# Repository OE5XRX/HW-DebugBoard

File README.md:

# HW-DebugBoard

Ein universelles Debug-Board für die OE5XRX-Modulplattform zur Entwicklung, Analyse und automatisierten Tests von Hardware-Modulen wie z. B. dem FM-Transceiver-Modul.

## Features

- USB-C + USB-Hub für:
  - Debug-STM32 (Firmwaretest)
  - ST-Link zur Programmierung
  - USB-Verbindung zum DUT
- Schnittstelle für genormte DUT-Module (2×10 Pin)
- INA226 für Strom- und Spannungsmessung
- OLED-Display und Taster zur Steuerung
- Erweiterbar durch GPIO, ADC, DAC, UARTs, I²C

## Projektstatus

🛠️ Derzeit in Schaltungsdesign-Phase (Schematic)

---

## ✅ To-do Liste (Schaltplan – Hierarchisch)

### 🔌 1. USB & USB-Hub (`usb_hub.sch`)
- [x] USB-C Buchse mit ESD-Schutz (TVS)
- [x] USB-Hub IC (z. B. FS1.1, TUSB2046B, GL850G)
- [x] Downstream-Port 1: Debug-STM32
- [x] Downstream-Port 2: ST-Link USB
- [x] Downstream-Port 3: DUT USB-Buchse
- [x] Taktquelle für USB-Hub (z. B. 12 MHz Quarz)
- [x] Serienwiderstände & Pull-Ups gemäß Datenblatt

### 🧠 2. Debug-Controller (`stm32.sch`)
- [x] STM32F302CBTx (LQFP-48)
- [x] Reset-Schaltung & ggf. Quarz
- [x] USB-Anbindung zum Hub
- [x] GPIO-Zuweisungen:
  - [x] I²C für OLED & INA226
  - [x] Taster (3×)
  - [x] DUT_RESET
  - [x] DUT_VCC_EN
  - [x] INA226_ALERT
- [x] Optional: eigene SWD-Schnittstelle

### 🧷 3. ST-Link Interface (`stlink.sch`)
- [x] USB-A Buchse oder Pfostenleiste für ST-Link-Verbindung
- [ ] Mechanik zur Befestigung des ST-Link (z. B. Kabelbinderloch)
- [x] Rückführung der SWD-Leitungen zum Board:
  - [x] Wannenstecker zu DUT
  - [x] Optional: Debug-STM32 Flashbarkeit

### 📟 4. Display & UI (`ui.sch`)
- [x] SSD1306 OLED über I²C
- [ ] I²C Pull-Ups (z. B. 4.7 kΩ)
- [x] 3 Taster mit Pull-Ups
- [x] GPIO-Zuweisungen zu STM32

### ⚡ 5. DUT Power Control (`power_switch.sch`)
- [x] Lastschalter - TPS22917
  - [x] Enable via STM32
  - [x] Versorgung 5V
- [x] Abblock-Cs, evtl. Reverse Protection
- [x] Spannungsversorgung zum DUT Header

### 📊 6. Strom-/Spannungsmessung (`ina226.sch`)
- [x] INA226 am I²C
- [x] Shunt-Widerstand (0.01 Ω, 1%, >0.5 W)
- [x] Alert-Signal an STM32
- [x] Serienschaltung im VCC Pfad zum DUT

### 🔁 7. DUT Interface Header (`hil_interface.sch`)
- [x] SHF-110-01-L-D-RA (2×10)
- [x] Finales Pinout definiert:
  - [x] UART0 TX/RX
  - [x] UART1 TX/RX
  - [x] I²C SDA/SCL
  - [x] ADC0, ADC1 mit AGND
  - [x] DAC_OUT mit AGND
  - [x] 3V3_SENSE
  - [x] GND mehrfach verteilt
- [ ] ESD-Schutz und Serienwiderstände prüfen
- [x] Labeling für Orientierung (z. B. Pin 1 Markierung)

### 🧩 8. Mechanik & DUT-Steckplatz (`dut_mech.sch`)
- [x] Horizontale Buchse für DUT-Modul
- [x] USB-Verbindung vom Hub zum DUT
- [ ] Mechanischer Bereich für Modul-Tausch
- [x] Optional: Schraublöcher / Führung
- [ ] Platz für FM-Modul sicherstellen

### 🛠️ 9. Globales & Hilfsfunktionen (`globals.sch`)
- [x] Power-Netze global (VBUS, 3V3, GND, etc.)
- [ ] Labeling (Silkscreen, Versionsnummer)
- [ ] I²C-Adressenübersicht
- [ ] Schutzbeschaltungen
- [ ] Board-ID optional

---

## 📄 License

This project is licensed under [CERN-OHL-S-2.0](https://choosealicense.com/licenses/cern-ohl-s-2.0/).

## 🧪 Badges

<br>
<br>
<br>
<br>
<br>

## 📬 Contact

OE5XRX Amateur Radio Club<br>
🌐 https://oe5xrx.org<br>
✉️ info@oe5xrx.org<br>

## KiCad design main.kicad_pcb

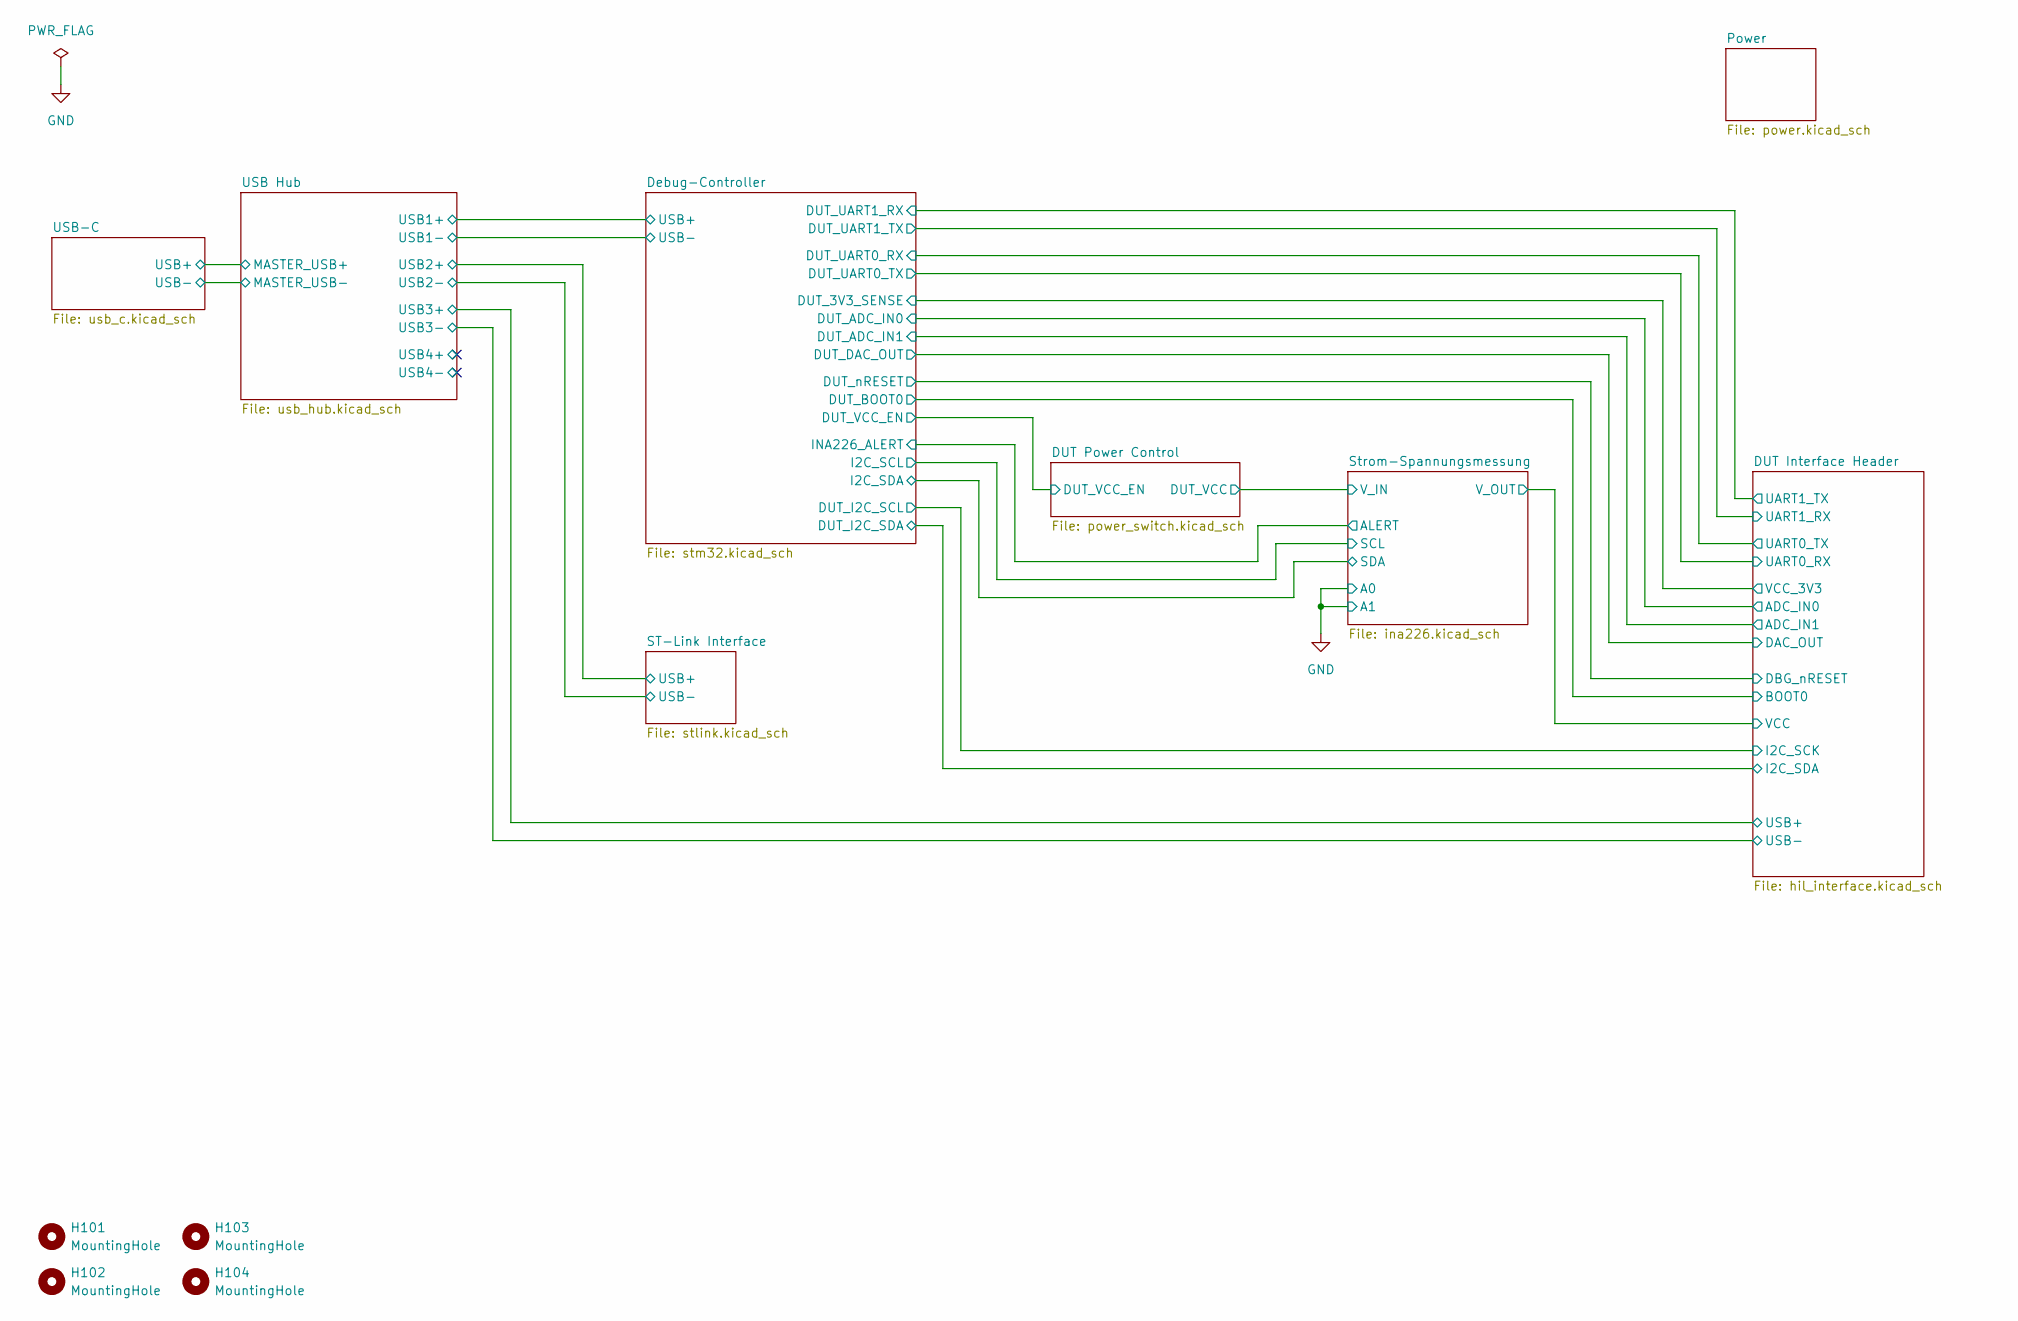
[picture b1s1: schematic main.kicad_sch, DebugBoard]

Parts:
H101, H102, H103, H104: MountingHole; MountingHole_3.2mm_M3

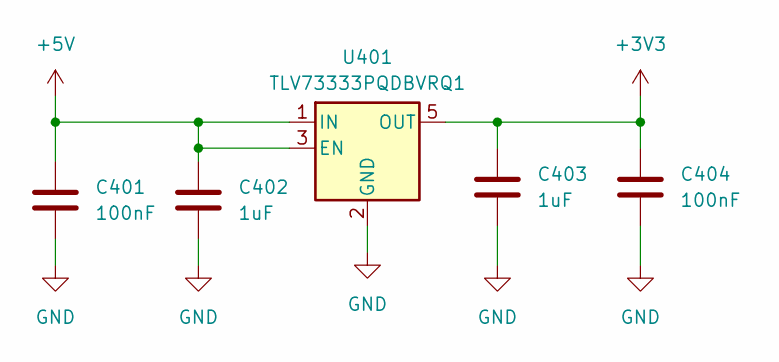
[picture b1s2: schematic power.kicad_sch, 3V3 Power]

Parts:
C401, C404: 100nF; C_0805_2012Metric; LCSC C28233
C402, C403: 1uF; C_0805_2012Metric; MOUSER 791-0805B105K250CT
U401: TLV73333PQDBVRQ1; SOT-23-5; LCSC C2862550

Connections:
+3V3: C403.1, C404.2, U401.5 (OUT); also elsewhere on the board
+5V: C401.2, C402.1, U401.1 (IN), U401.3 (EN); also elsewhere on the board
GND: C401.1, C402.2, C403.2, C404.1, U401.2 (GND); also elsewhere on the board

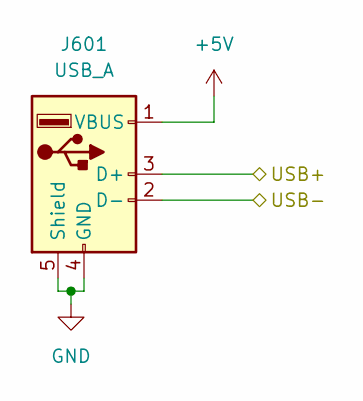
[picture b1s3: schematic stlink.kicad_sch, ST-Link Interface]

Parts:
J601: USB_A; USB_A_Molex_67643_Horizontal; MOUSER 538-67643-0910

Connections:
+5V: J601.1 (VBUS); also elsewhere on the board
/ST-Link Interface/USB+: J601.3 (D+); also elsewhere on the board
/ST-Link Interface/USB-: J601.2 (D-); also elsewhere on the board
GND: J601.4 (GND), J601.5 (Shield); also elsewhere on the board

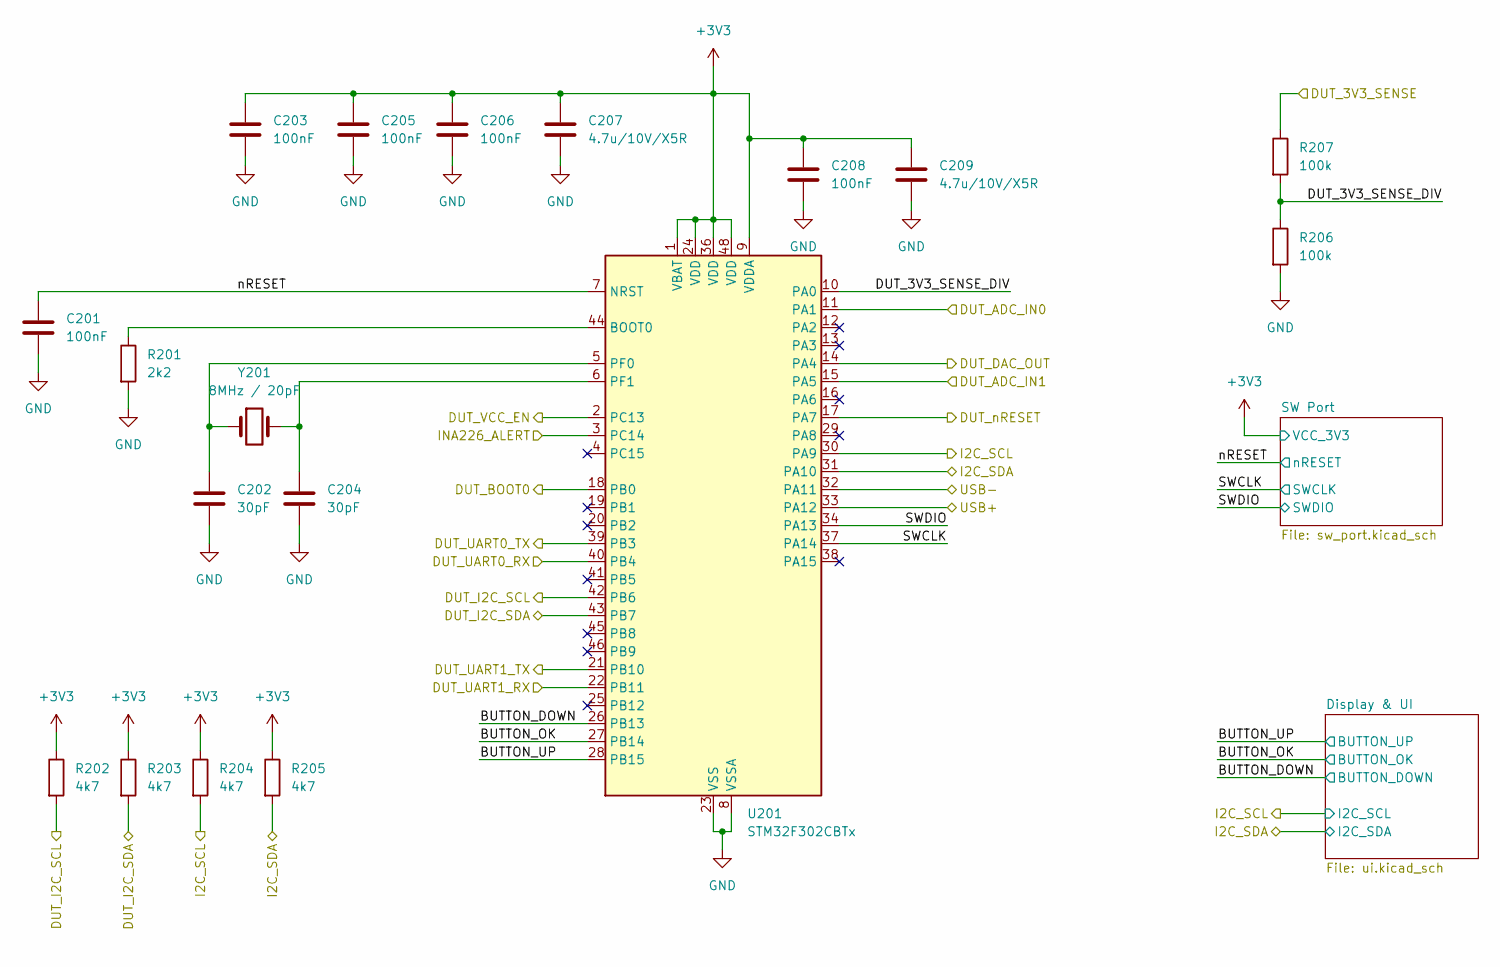
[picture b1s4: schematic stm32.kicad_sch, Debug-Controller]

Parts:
C201, C203, C205, C206, C208: 100nF; C_0805_2012Metric; LCSC C28233
C202, C204: 30pF; C_0805_2012Metric; MOUSER 791-0805N300J500CT
C207, C209: 4.7u/10V/X5R; C_0805_2012Metric; MOUSER 187-CL21A475KAQNNNF
R201: 2k2; R_0805_2012Metric; LCSC C17520
R202, R203, R204, R205: 4k7; R_0805_2012Metric
R206, R207: 100k; R_0805_2012Metric
U201: STM32F302CBTx; LQFP-48_7x7mm_P0.5mm; MOUSER 511-STM32F302CBT7
Y201: 8MHz / 20pF; Crystal_SMD_HC49-SD; MOUSER 73-XT49M800-20

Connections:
+3V3: C203.2, C205.2, C206.2, C207.2, C208.2, C209.2, R202.1, R203.1, R204.1, R205.1, U201.1 (VBAT), U201.9 (VDDA), U201.24 (VDD), U201.36 (VDD), U201.48 (VDD); also elsewhere on the board
/DUT Interface Header/ADC_IN0: U201.11 (PA1); also elsewhere on the board
/DUT Interface Header/ADC_IN1: U201.15 (PA5); also elsewhere on the board
/DUT Interface Header/BOOT0: U201.18 (PB0); also elsewhere on the board
/DUT Interface Header/DAC_OUT: U201.14 (PA4); also elsewhere on the board
/DUT Interface Header/DBG_nRESET: U201.17 (PA7); also elsewhere on the board
/DUT Interface Header/I2C_SCK: R202.2, U201.42 (PB6); also elsewhere on the board
/DUT Interface Header/I2C_SDA: R203.2, U201.43 (PB7); also elsewhere on the board
/DUT Interface Header/UART0_RX: U201.39 (PB3); also elsewhere on the board
/DUT Interface Header/UART0_TX: U201.40 (PB4); also elsewhere on the board
/DUT Interface Header/UART1_RX: U201.21 (PB10); also elsewhere on the board
/DUT Interface Header/UART1_TX: U201.22 (PB11); also elsewhere on the board
/DUT Interface Header/VCC_3V3: R207.1; also elsewhere on the board
/DUT Power Control/DUT_VCC_EN: U201.2 (PC13); also elsewhere on the board
/Debug-Controller/BUTTON_DOWN: U201.26 (PB13); also elsewhere on the board
/Debug-Controller/BUTTON_OK: U201.27 (PB14); also elsewhere on the board
/Debug-Controller/BUTTON_UP: U201.28 (PB15); also elsewhere on the board
/Debug-Controller/DUT_3V3_SENSE_DIV: R206.1, R207.2, U201.10 (PA0)
/Debug-Controller/I2C_SCL: R204.2, U201.30 (PA9); also elsewhere on the board
/Debug-Controller/I2C_SDA: R205.2, U201.31 (PA10); also elsewhere on the board
/Debug-Controller/INA226_ALERT: U201.3 (PC14); also elsewhere on the board
/Debug-Controller/SWCLK: U201.37 (PA14); also elsewhere on the board
/Debug-Controller/SWDIO: U201.34 (PA13); also elsewhere on the board
/Debug-Controller/USB+: U201.33 (PA12); also elsewhere on the board
/Debug-Controller/USB-: U201.32 (PA11); also elsewhere on the board
/Debug-Controller/nRESET: C201.1, U201.7 (NRST); also elsewhere on the board
GND: C201.2, C202.2, C203.1, C204.2, C205.1, C206.1, C207.1, C208.1, C209.1, R201.2, R206.2, U201.8 (VSSA), U201.23 (VSS), U201.35 (VSS), U201.47 (VSS); also elsewhere on the board
unnamed: R201.1, U201.44 (BOOT0)
unnamed: C202.1, U201.5 (PF0), Y201.1
unnamed: C204.1, U201.6 (PF1), Y201.2

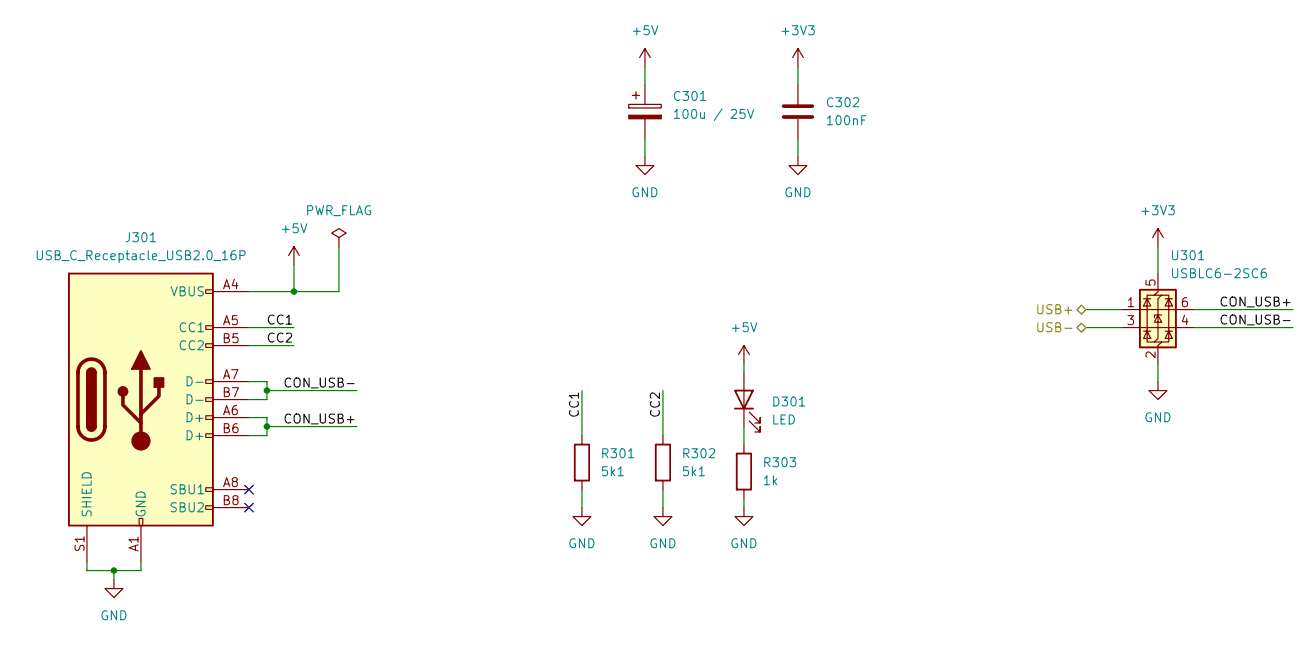
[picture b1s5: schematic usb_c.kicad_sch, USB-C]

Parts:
C301: 100u / 25V; CP_EIA-7343-43_Kemet-X; LCSC C132558
C302: 100nF; C_0805_2012Metric; LCSC C28233
D301: LED; LED_0805_2012Metric; LCSC C84256
J301: USB_C_Receptacle_USB2.0_16P; USB_C_Receptacle_G-Switch_GT-USB-7010ASV; LCSC C2988369
R301, R302: 5k1; R_0805_2012Metric; LCSC C27834
R303: 1k; R_0805_2012Metric; LCSC C17513
U301: USBLC6-2SC6; SOT-23-6; LCSC C2827654

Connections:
+3V3: C302.1, U301.5 (VBUS); also elsewhere on the board
+5V: C301.1, D301.2 (A), J301.A4 (VBUS), J301.A9 (VBUS), J301.B4 (VBUS), J301.B9 (VBUS); also elsewhere on the board
/USB Hub/MASTER_USB+: U301.1 (I/O1); also elsewhere on the board
/USB Hub/MASTER_USB-: U301.3 (I/O2); also elsewhere on the board
/USB-C/CC1: J301.A5 (CC1), R301.1
/USB-C/CC2: J301.B5 (CC2), R302.1
/USB-C/CON_USB+: J301.A6 (D+), J301.B6 (D+), U301.6 (I/O1)
/USB-C/CON_USB-: J301.A7 (D-), J301.B7 (D-), U301.4 (I/O2)
GND: C301.2, C302.2, J301.A1 (GND), J301.A12 (GND), J301.B1 (GND), J301.B12 (GND), J301.S1 (SHIELD), R301.2, R302.2, R303.2, U301.2 (GND); also elsewhere on the board
unnamed: D301.1 (K), R303.1

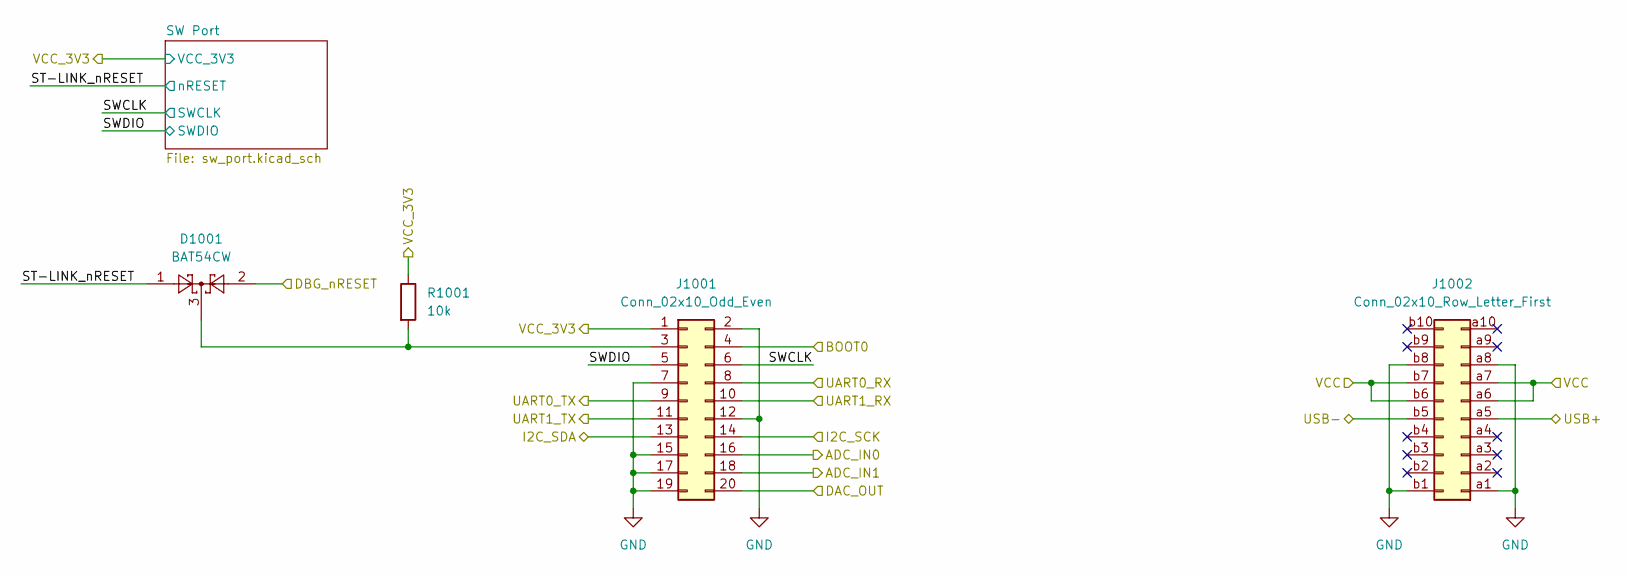
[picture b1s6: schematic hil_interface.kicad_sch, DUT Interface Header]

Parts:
D1001: BAT54CW; SOT-323_SC-70
J1001: Conn_02x10_Odd_Even; PinHeader_2x10_P1.27mm_Vertical
J1002: Conn_02x10_Row_Letter_First; PCN10-20P-2.54DS; MOUSER 798-PCN1020P254DS72
R1001: 10k; R_0805_2012Metric

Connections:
/DUT Interface Header/ADC_IN0: J1001.16; also elsewhere on the board
/DUT Interface Header/ADC_IN1: J1001.18; also elsewhere on the board
/DUT Interface Header/BOOT0: J1001.4; also elsewhere on the board
/DUT Interface Header/DAC_OUT: J1001.20; also elsewhere on the board
/DUT Interface Header/DBG_nRESET: D1001.2; also elsewhere on the board
/DUT Interface Header/I2C_SCK: J1001.14; also elsewhere on the board
/DUT Interface Header/I2C_SDA: J1001.13; also elsewhere on the board
/DUT Interface Header/ST-LINK_nRESET: D1001.1; also elsewhere on the board
/DUT Interface Header/SWCLK: J1001.6; also elsewhere on the board
/DUT Interface Header/SWDIO: J1001.5; also elsewhere on the board
/DUT Interface Header/UART0_RX: J1001.8; also elsewhere on the board
/DUT Interface Header/UART0_TX: J1001.9; also elsewhere on the board
/DUT Interface Header/UART1_RX: J1001.10; also elsewhere on the board
/DUT Interface Header/UART1_TX: J1001.11; also elsewhere on the board
/DUT Interface Header/USB+: J1002.a5; also elsewhere on the board
/DUT Interface Header/USB-: J1002.b5; also elsewhere on the board
/DUT Interface Header/VCC: J1002.a6, J1002.a7, J1002.b6, J1002.b7; also elsewhere on the board
/DUT Interface Header/VCC_3V3: J1001.1, R1001.1; also elsewhere on the board
GND: J1001.2, J1001.7, J1001.12, J1001.15, J1001.17, J1001.19, J1002.a1, J1002.a8, J1002.b1, J1002.b8; also elsewhere on the board
unnamed: D1001.3, J1001.3, R1001.2

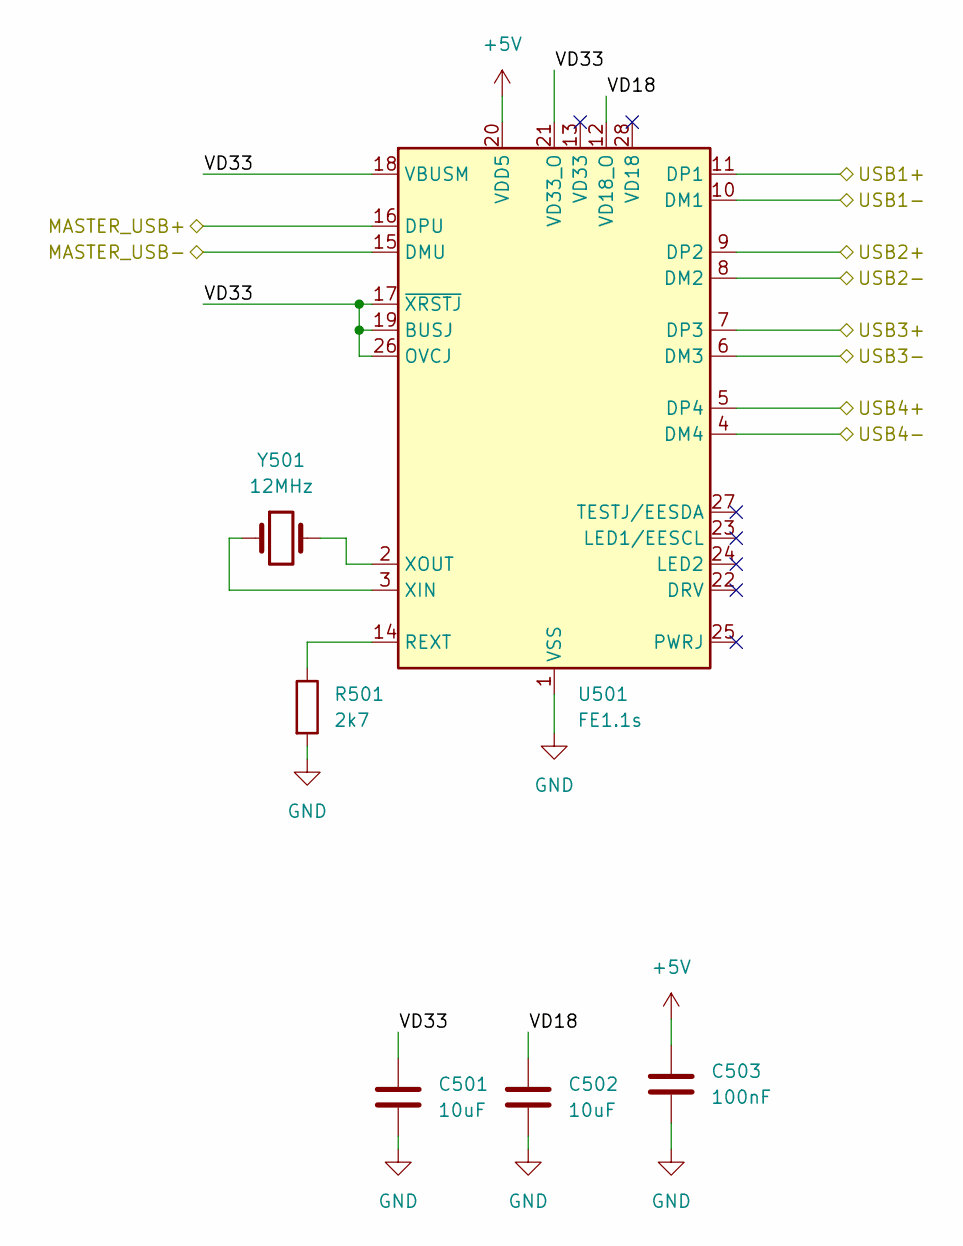
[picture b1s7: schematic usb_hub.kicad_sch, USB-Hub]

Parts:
C501, C502: 10uF; C_0805_2012Metric; LCSC C13585
C503: 100nF; C_0805_2012Metric; LCSC C28233
R501: 2k7; R_0805_2012Metric; LCSC C352230
U501: FE1.1s; SSOP-28_3.9x9.9mm_P0.635mm; LCSC C6706491
Y501: 12MHz; M49S-SMD; LCSC C2983432

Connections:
+5V: C503.1, U501.20 (VDD5); also elsewhere on the board
/DUT Interface Header/USB+: U501.7 (DP3); also elsewhere on the board
/DUT Interface Header/USB-: U501.6 (DM3); also elsewhere on the board
/Debug-Controller/USB+: U501.11 (DP1); also elsewhere on the board
/Debug-Controller/USB-: U501.10 (DM1); also elsewhere on the board
/ST-Link Interface/USB+: U501.9 (DP2); also elsewhere on the board
/ST-Link Interface/USB-: U501.8 (DM2); also elsewhere on the board
/USB Hub/MASTER_USB+: U501.16 (DPU); also elsewhere on the board
/USB Hub/MASTER_USB-: U501.15 (DMU); also elsewhere on the board
/USB Hub/USB4+: U501.5 (DP4)
/USB Hub/USB4-: U501.4 (DM4)
/USB Hub/VD18: C502.1, U501.12 (VD18_O)
/USB Hub/VD33: C501.1, U501.17 (~XRSTJ), U501.18 (VBUSM), U501.19 (BUSJ), U501.21 (VD33_O), U501.26 (OVCJ)
GND: C501.2, C502.2, C503.2, R501.2, U501.1 (VSS); also elsewhere on the board
unnamed: R501.1, U501.14 (REXT)
unnamed: U501.3 (XIN), Y501.1
unnamed: U501.2 (XOUT), Y501.2

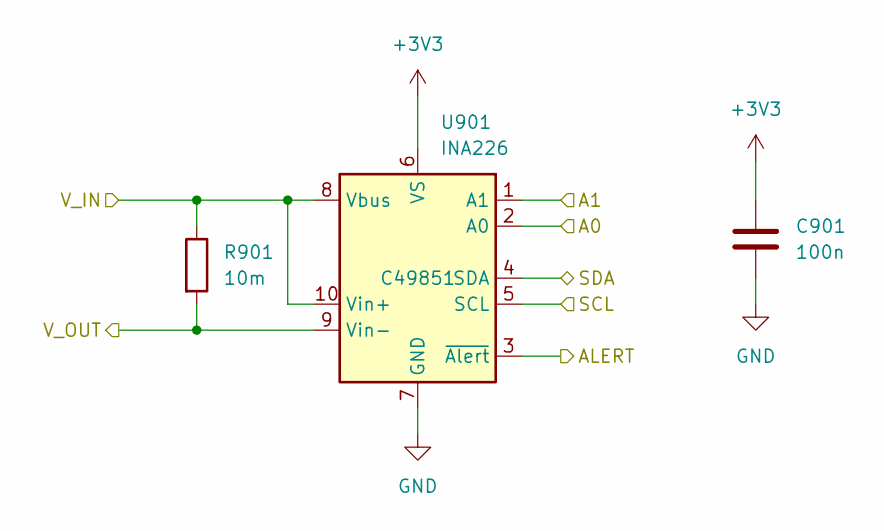
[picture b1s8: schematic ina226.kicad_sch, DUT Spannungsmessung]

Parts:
C901: 100n; C_0805_2012Metric; LCSC C28233
R901: 10m; R_2512_6332Metric; MOUSER 652-CRF2512FZR010ELF
U901: INA226; VSSOP-10_3x3mm_P0.5mm; LCSC C49851

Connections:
+3V3: C901.1, U901.6 (VS); also elsewhere on the board
/DUT Interface Header/VCC: R901.2, U901.9 (Vin-); also elsewhere on the board
/DUT Power Control/DUT_VCC: R901.1, U901.8 (Vbus), U901.10 (Vin+); also elsewhere on the board
/Debug-Controller/I2C_SCL: U901.5 (SCL); also elsewhere on the board
/Debug-Controller/I2C_SDA: U901.4 (SDA); also elsewhere on the board
/Debug-Controller/INA226_ALERT: U901.3 (~Alert); also elsewhere on the board
GND: C901.2, U901.1 (A1), U901.2 (A0), U901.7 (GND); also elsewhere on the board

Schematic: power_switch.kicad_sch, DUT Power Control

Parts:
C801, C802: 4.7u/10V/X5R; C_0805_2012Metric; MOUSER 187-CL21A475KAQNNNF
U801: TPS22917DBV; SOT-23-6

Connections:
+5V: C801.2, U801.1 (VIN); also elsewhere on the board
/DUT Power Control/DUT_VCC: C802.2, U801.6 (VOUT); also elsewhere on the board
/DUT Power Control/DUT_VCC_EN: U801.3 (ON); also elsewhere on the board
GND: C801.1, C802.1, U801.2 (GND); also elsewhere on the board

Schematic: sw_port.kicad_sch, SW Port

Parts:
J1101: Conn_02x05_Odd_Even

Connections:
+3V3: J1101.7, J1101.8; also elsewhere on the board
/Debug-Controller/SWCLK: J1101.6; also elsewhere on the board
/Debug-Controller/SWDIO: J1101.2; also elsewhere on the board
/Debug-Controller/nRESET: J1101.1; also elsewhere on the board
GND: J1101.3, J1101.4; also elsewhere on the board

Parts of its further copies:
J1201: Conn_02x05_Odd_Even

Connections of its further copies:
/DUT Interface Header/ST-LINK_nRESET: J1201.1; also elsewhere on the board
/DUT Interface Header/SWCLK: J1201.6; also elsewhere on the board
/DUT Interface Header/SWDIO: J1201.2; also elsewhere on the board
/DUT Interface Header/VCC_3V3: J1201.7, J1201.8; also elsewhere on the board
GND: J1201.3, J1201.4; also elsewhere on the board

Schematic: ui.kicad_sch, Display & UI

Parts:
Brd701: SSD1306; 128x64OLED
SW701, SW702, SW703: SW_Push

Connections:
+3V3: Brd701.2 (VCC); also elsewhere on the board
/Debug-Controller/BUTTON_DOWN: SW703.1; also elsewhere on the board
/Debug-Controller/BUTTON_OK: SW702.1; also elsewhere on the board
/Debug-Controller/BUTTON_UP: SW701.1; also elsewhere on the board
/Debug-Controller/I2C_SCL: Brd701.3 (SCL); also elsewhere on the board
/Debug-Controller/I2C_SDA: Brd701.4 (SDA); also elsewhere on the board
GND: Brd701.1 (GND), SW701.2, SW702.2, SW703.2; also elsewhere on the board

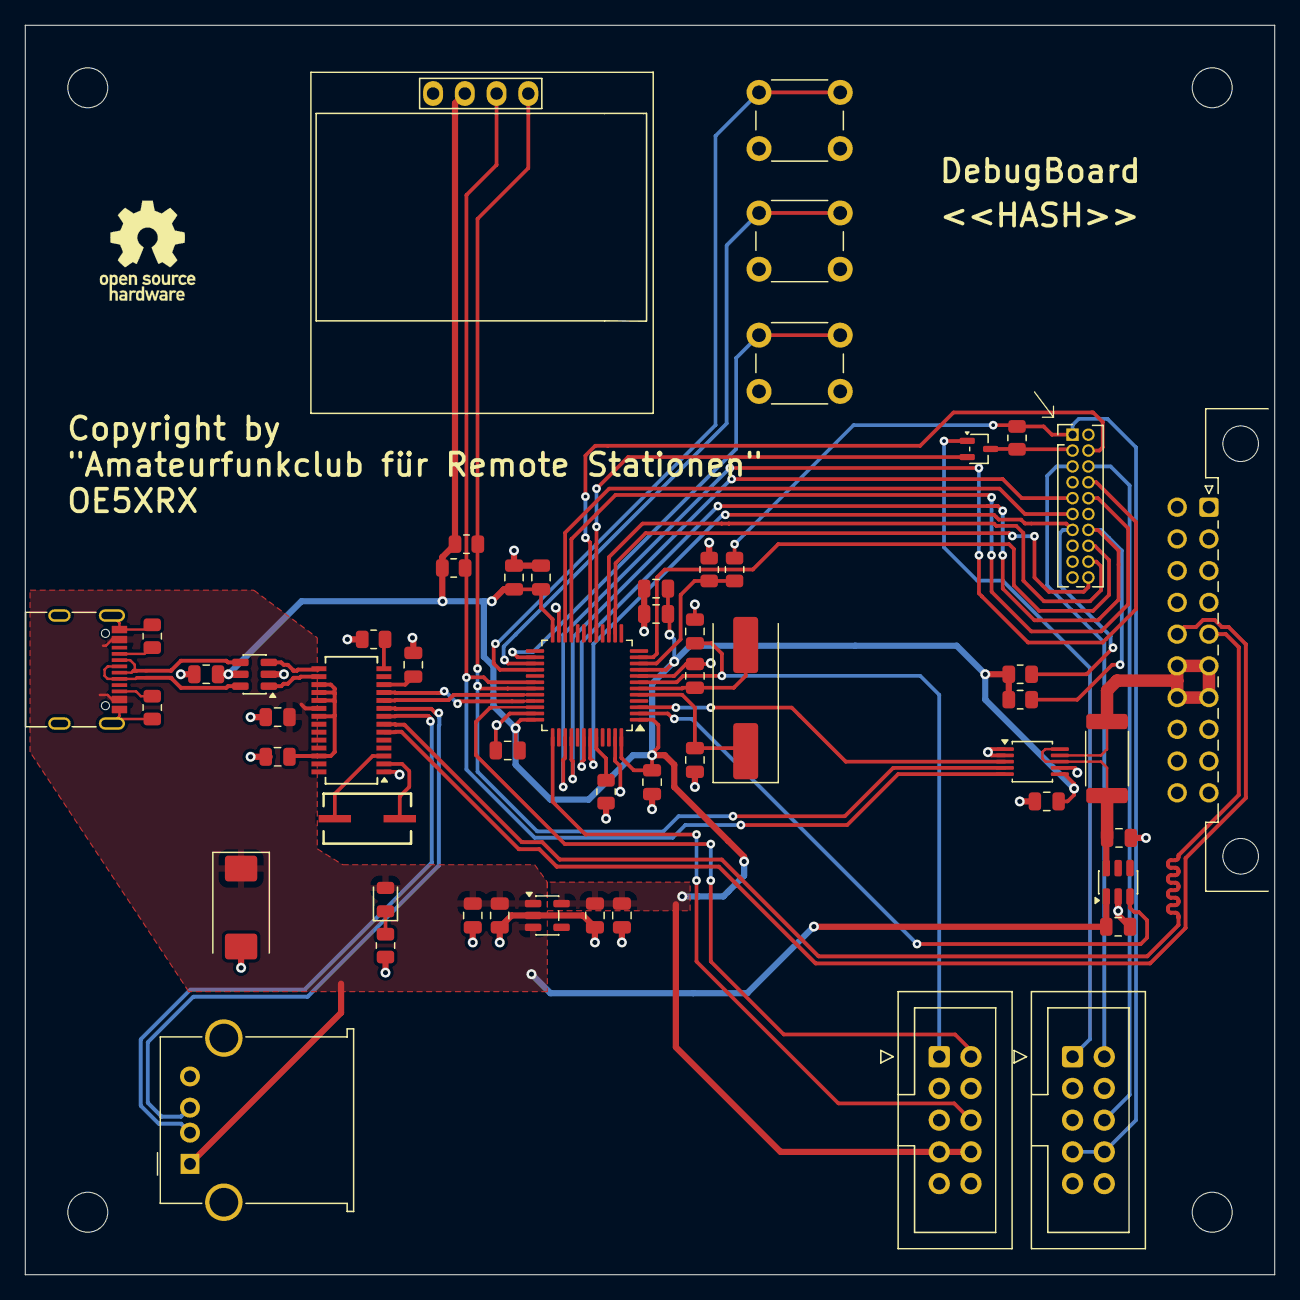
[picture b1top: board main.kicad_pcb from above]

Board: 4 copper layers, 100.0 x 100.0 mm, 58 parts (0 on the bottom side), 53 nets.

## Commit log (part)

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2026-01-06 Update README and documentation for HW-DebugBoard; remove unused .gitkeep files
2026-01-06 add first KiCad version
2026-01-06 add basic structure, update readme
2026-01-08 Update schematic for DebugBoard with connector and power symbols.
2026-01-10 Update USB-C and USB-Hub Schematics with New Titles and Reference Changes
    - Changed title from "DebugBoard" to "USB-C" in usb_c.kicad_sch.
    - Changed title from "DebugBoard" to "USB-Hub" in usb_hub.kicad_sch.
    - Updated multiple component references in usb_c.kicad_sch to new identifiers (#PWR0301 to #PWR0312, D301, U301, etc.).
    - Updated component reference from "R103" to "R501" in usb_hub.kicad_sch.
2026-01-11 Refactor code structure for improved readability and maintainability
2026-03-06 update pcb
2026-05-12 refactor(ci): replace workflows with HW-Module-CI thin wrappers
2026-05-12 chore(ci): delete files now provided by HW-Module-CI; remove sync source role
2026-05-12 feat(docs): migrate index.md to Jekyll Liquid for output paths
2026-05-12 chore: ignore CI-generated doc/_data/project.yml
2026-05-12 rename(kicad): main.kicad_* → DebugBoard.kicad_*

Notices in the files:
README.md:
License: CERN-OHL-S
main.kicad_pcb:
Copyright by
{dblquote}Amateurfunkclub für Remote Stationen{dblquote}
